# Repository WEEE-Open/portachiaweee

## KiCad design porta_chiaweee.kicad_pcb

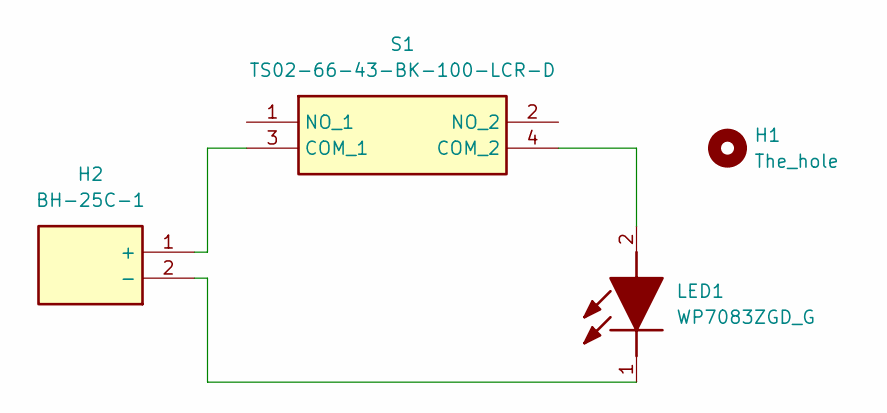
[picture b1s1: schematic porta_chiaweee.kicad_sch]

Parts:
H1: The_hole; MountingHole_5.3mm_M5_DIN965_Pad_TopBottom
H2: BH-25C-1; BH25C1; Mouser Part Number 737-BH-25C-1
LED1: WP7083ZGD_G; L53ND; Mouser Part Number 604-WP7083ZGD/G
S1: TS02-66-43-BK-100-LCR-D; TS026643BK100LCRD; Mouser Part Number 179-TS026643BK100LCR

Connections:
unnamed: H2.1 (+), S1.3 (COM_1)
unnamed: H2.2 (-), LED1.1 (K)
unnamed: LED1.2 (A), S1.4 (COM_2)

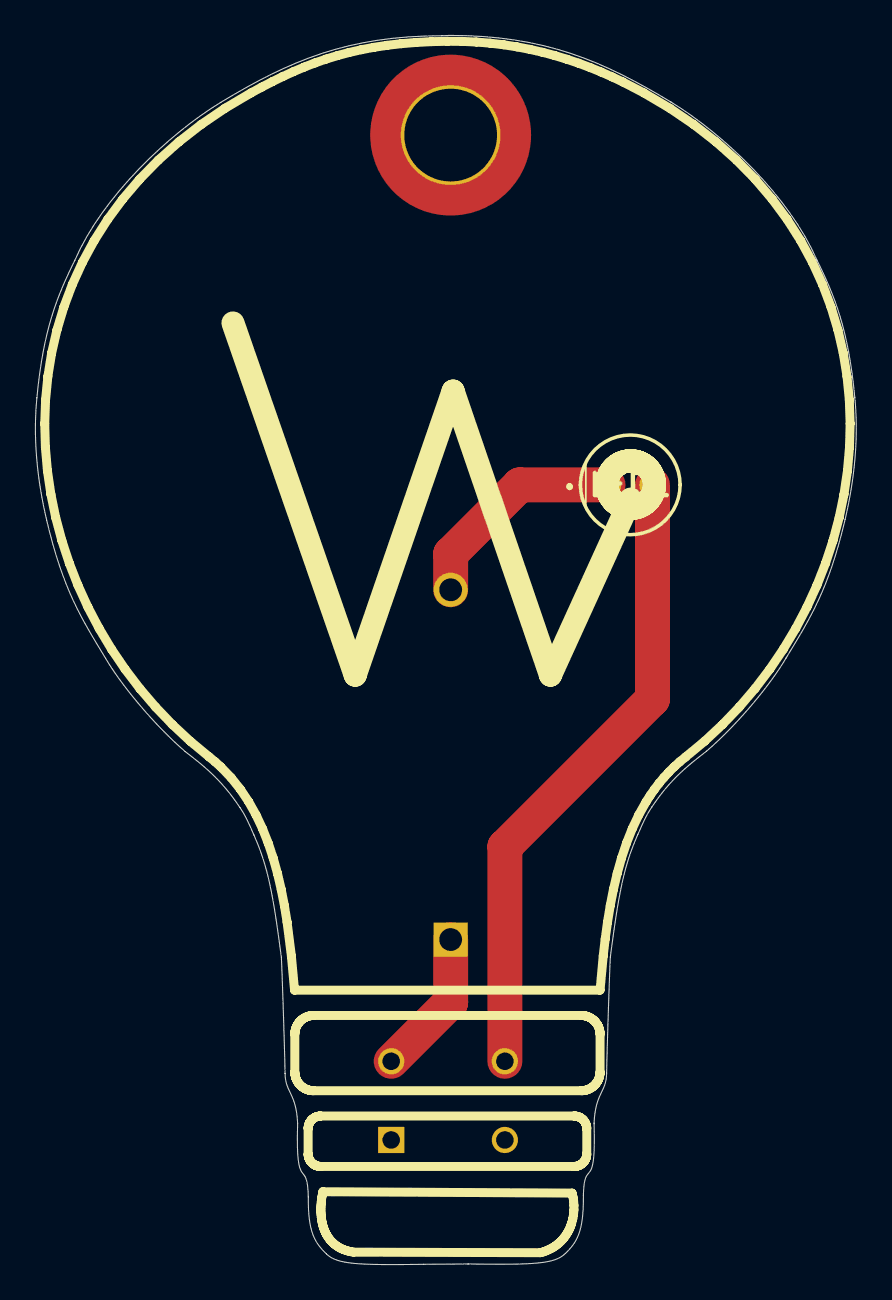
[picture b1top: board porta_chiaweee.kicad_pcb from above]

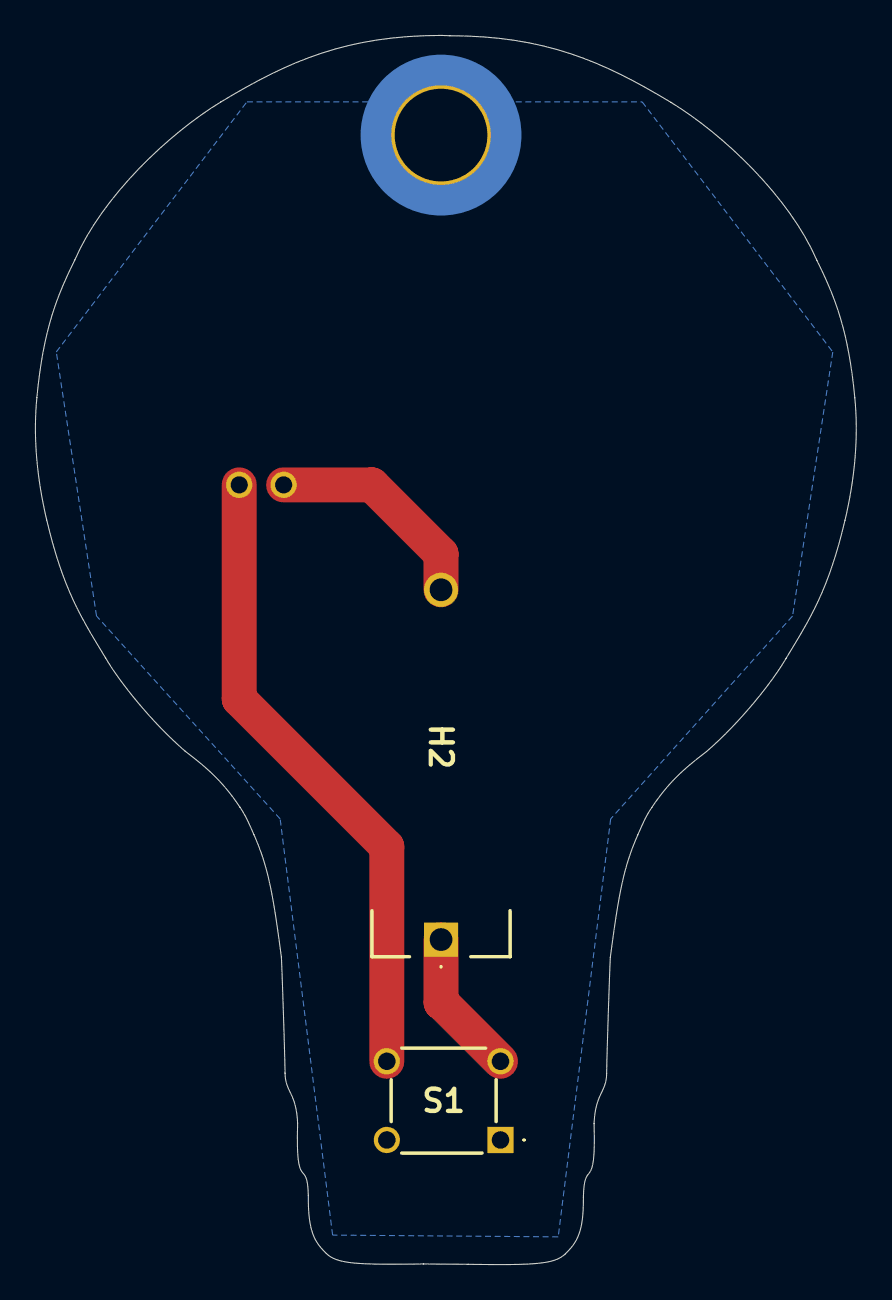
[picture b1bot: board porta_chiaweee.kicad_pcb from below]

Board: 2 copper layers, 46.9 x 70.3 mm, 4 parts (2 on the bottom side), 3 nets.

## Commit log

2026-05-21 test per plugin git su kicad
2026-05-21 forma pcb e buco
2026-05-22 aggiunte librerie nuove e modelli 3D
2026-05-26 rooting e nuovo bordo
2026-05-28 aggiunto piano di massa
